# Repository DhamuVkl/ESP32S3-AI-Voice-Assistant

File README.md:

# Design your own AI voice assistant 

*A fully custom, open-source AI voice assistant powered by ESP32-S3 and Xiaozhi AI framework*

</div>

---

## 📋 Overview

This project is a complete DIY AI voice assistant built around the ESP32-S3 microcontroller. It combines custom PCB design, advanced audio processing, and cloud-based AI to create a device that rivals commercial smart speakers in functionality while remaining fully open-source and customizable.

Unlike simple voice-controlled devices, this assistant leverages the **Xiaozhi AI framework** to provide natural language understanding through large language models (LLMs) like Qwen, DeepSeek, and GPT. The system uses a hybrid architecture: lightweight tasks run locally on the ESP32-S3, while computationally intensive AI processing happens on cloud servers.

### Key Highlights

- ✨ **Natural Conversation**: Powered by modern LLMs for intelligent, context-aware responses
- 🎙️ **Dual-Microphone Array**: Advanced audio capture with beamforming and echo cancellation
- 🔋 **Battery Powered**: Complete power management with USB-C charging and portable operation
- 💡 **WS2812B LED Ring**: Visual feedback with customizable animations
- 🏠 **Smart Home Ready**: Integration with Home Assistant and other platforms
- 🔧 **Fully Customizable**: Open hardware and software for endless possibilities
- 📱 **Web-Based Control**: Easy configuration through Xiaozhi console
- 🌐 **Multi-Language**: Support for multiple languages depending on AI model

---

## 🎯 Features

### Hardware Features
- **ESP32-S3-WROOM-1-N16R8** (Dual-core, 16MB Flash, 8MB PSRAM)
- **Dual ICS-43434 MEMS Microphones** for superior audio capture
- **MAX98357A I²S Amplifier** driving 3W speaker
- **BQ24250 Li-Ion Charger** with USB-C power delivery
- **MAX20402 Buck-Boost Regulator** for stable 3.3V output
- **WS2812B RGB LED Ring** for visual status indication
- **Optional OLED Display** header for screen integration
- **Compact PCB Design** (2-layer, professionally fabricated)
- **Custom 3D-Printed Enclosure** optimized for acoustics

### Software Features
- **Wake Word Detection** using Espressif's WakeNet
- **Audio Front-End (AFE)** with noise reduction and echo cancellation
- **WebSocket Communication** for low-latency server connection
- **Multiple AI Models** (Qwen, DeepSeek, GPT-4, and more)
- **Conversation History** and context awareness
- **Voice Profile Support** for personalized responses
- **Smart Home Integration** via Xiaozhi skill marketplace
- **OTA Updates** for firmware upgrades
- **Battery Monitoring** with low-battery alerts

---

## 🛠️ Hardware

### Bill of Materials (BOM)

| Component | Part Number | Quantity | Notes |
|-----------|------------|----------|-------|
| Microcontroller | ESP32-S3-WROOM-1-N16R8 | 1 | Main processor |
| Microphones | TDK InvenSense ICS-43434 | 2 | Digital MEMS |
| Audio Amplifier | MAX98357AETE+ | 1 | Class-D I²S |
| Battery Charger | BQ24250RGER | 1 | Li-Ion charging IC |
| DC-DC Converter | MAX20402ATGA/+ | 1 | Buck-boost regulator |
| RGB LEDs | WS2812B-5050 | 8-12 | Addressable LEDs |
| USB-C Connector | USB4105-GF-A | 1 | Power & programming |
| Speaker | 3W 4Ω Cavity Speaker | 1 | Audio output |
| Battery | Li-Ion/LiPo 3.7V | 1 | 2000-3000mAh recommended |
| Capacitors | Various (0603/0805) | ~25 | See full BOM |
| Resistors | Various (0603) | ~15 | See full BOM |
| Switches | 6x6mm Tactile | 2 | Reset & Boot |
| TVS Diode | USBLC6-2SC6 | 1 | USB ESD protection |

**📥 Full BOM with part numbers**: [Download BOM.csv](Hardware/PCB/BOM/ESP-AI-Assistant-BOM.xlsx)

### PCB Design

The custom PCB is a 2-layer design measuring approximately 80x60mm with careful attention to:
- Signal integrity for I²S audio
- Power distribution with minimal noise
- Thermal management for power ICs
- Acoustic isolation between microphones and speaker

### 3D Enclosure

The enclosure is designed for FDM 3D printing with features for:
- Acoustic optimization (speaker grille, microphone ports)
- LED light diffusion ring
- USB-C and button access
- Battery compartment
- Ventilation slots

## 🚀 Getting Started

### Prerequisites

**Hardware Tools**:
- Soldering iron and supplies
- Multimeter for testing
- USB-C cable (data capable)
- 3D printer (optional, for enclosure)

**Software Requirements**:
- [Visual Studio Code](https://code.visualstudio.com/)
- [ESP-IDF Extension for VS Code](https://marketplace.visualstudio.com/items?itemName=espressif.esp-idf-extension)
- ESP-IDF v5.4 or newer
- Git

### Step 1: Hardware Assembly

1. **Order PCB**: Upload `hardware/gerbers/gerbers.zip` to JLCPCB, PCBWay, or ALLPCB
2. **Source Components**: Use the BOM to order parts from DigiKey, Mouser, or LCSC
3. **Assemble PCB**: Follow the assembly guide for soldering instructions
4. **3D Print Enclosure**: Print the STL files and assemble

### Step 2: WiFi Configuration

On first boot, the device creates a WiFi access point:

1. Connect to WiFi network: `Xioazhi`
2. Navigate to `http://192.168.4.1`
3. Enter your WiFi credentials
4. Device will restart and connect to your network

**Alternative**: Configure WiFi via `idf.py menuconfig` before flashing

### Step 3: Xiaozhi Cloud Setup

1. Create account at [xiaozhi.me](https://xiaozhi.me)
2. Navigate to [Console → Agents](https://xiaozhi.me/console/agents)
3. Click "Add Device" to generate Device ID and Pairing Code
4. Device will auto-pair on first cloud connection
5. Customize AI personality, voice, and skills through console

### Step 4: Test Your Assistant

1. Say the wake word: **"Hey Wanda"**
2. Wait for LED confirmation (blue pulse)
3. Speak your question or command
4. Assistant responds through speaker
5. LED returns to idle state

---

## 🤝 Contributing

Contributions are welcome! Here's how you can help:

### Reporting Bugs
- Use GitHub Issues with detailed reproduction steps
- Include serial monitor logs
- Specify hardware revision and firmware version

### Feature Requests
- Open a GitHub Issue with [Feature Request] tag
- Describe use case and benefits
- Discuss implementation approach

**Contribution Guidelines**: [CONTRIBUTING.md](CONTRIBUTING.md)

---

## 📊 Project Status

- [x] PCB Design and fabrication
- [x] Firmware core functionality
- [x] Xiaozhi cloud integration
- [x] Basic voice interaction
- [x] 3D enclosure design
- [ ] Multi-device mesh networking
- [ ] Offline mode with local LLM
- [ ] Custom wake word training tools
- [ ] Mobile app for configuration
- [ ] Additional language packs

---

## 🔗 Related Projects

- [Xiaozhi ESP32](https://github.com/78/xiaozhi-esp32) - Official Xiaozhi firmware
- [ESP-IDF](https://github.com/espressif/esp-idf) - Espressif IoT Development Framework
- [WakeNet](https://github.com/espressif/esp-sr) - Espressif speech recognition
- [Home Assistant](https://www.home-assistant.io/) - Smart home integration

---

## 📄 License

This project is licensed under the MIT License - see [LICENSE](LICENSE) for details.

### Third-Party Licenses
- ESP-IDF: Apache 2.0
- Xiaozhi Framework: MIT
- Component datasheets: Respective manufacturers

---

## 🙏 Acknowledgments

- **Espressif Systems** for the amazing ESP32-S3 platform and development tools
- **Xiaozhi Team** for creating and maintaining the AI framework
- **Open-source community** for countless libraries and examples
- **PCB manufacturers** (JLCPCB, PCBWay) for affordable prototyping
- **Everyone** who contributed feedback, testing, and improvements

---

**Xiaozhi Community**:
- Forum: [xiaozhi.me/community](https://xiaozhi.me/community)
- Documentation: [docs.xiaozhi.me](https://docs.xiaozhi.me)

<div align="center">

**Built with ❤️ by makers, for makers**

[Documentation](docs/) • [Hardware Files](hardware/) • [Firmware](firmware/) • [Community](https://github.com/yourusername/esp32s3-voice-assistant/discussions)

</div>

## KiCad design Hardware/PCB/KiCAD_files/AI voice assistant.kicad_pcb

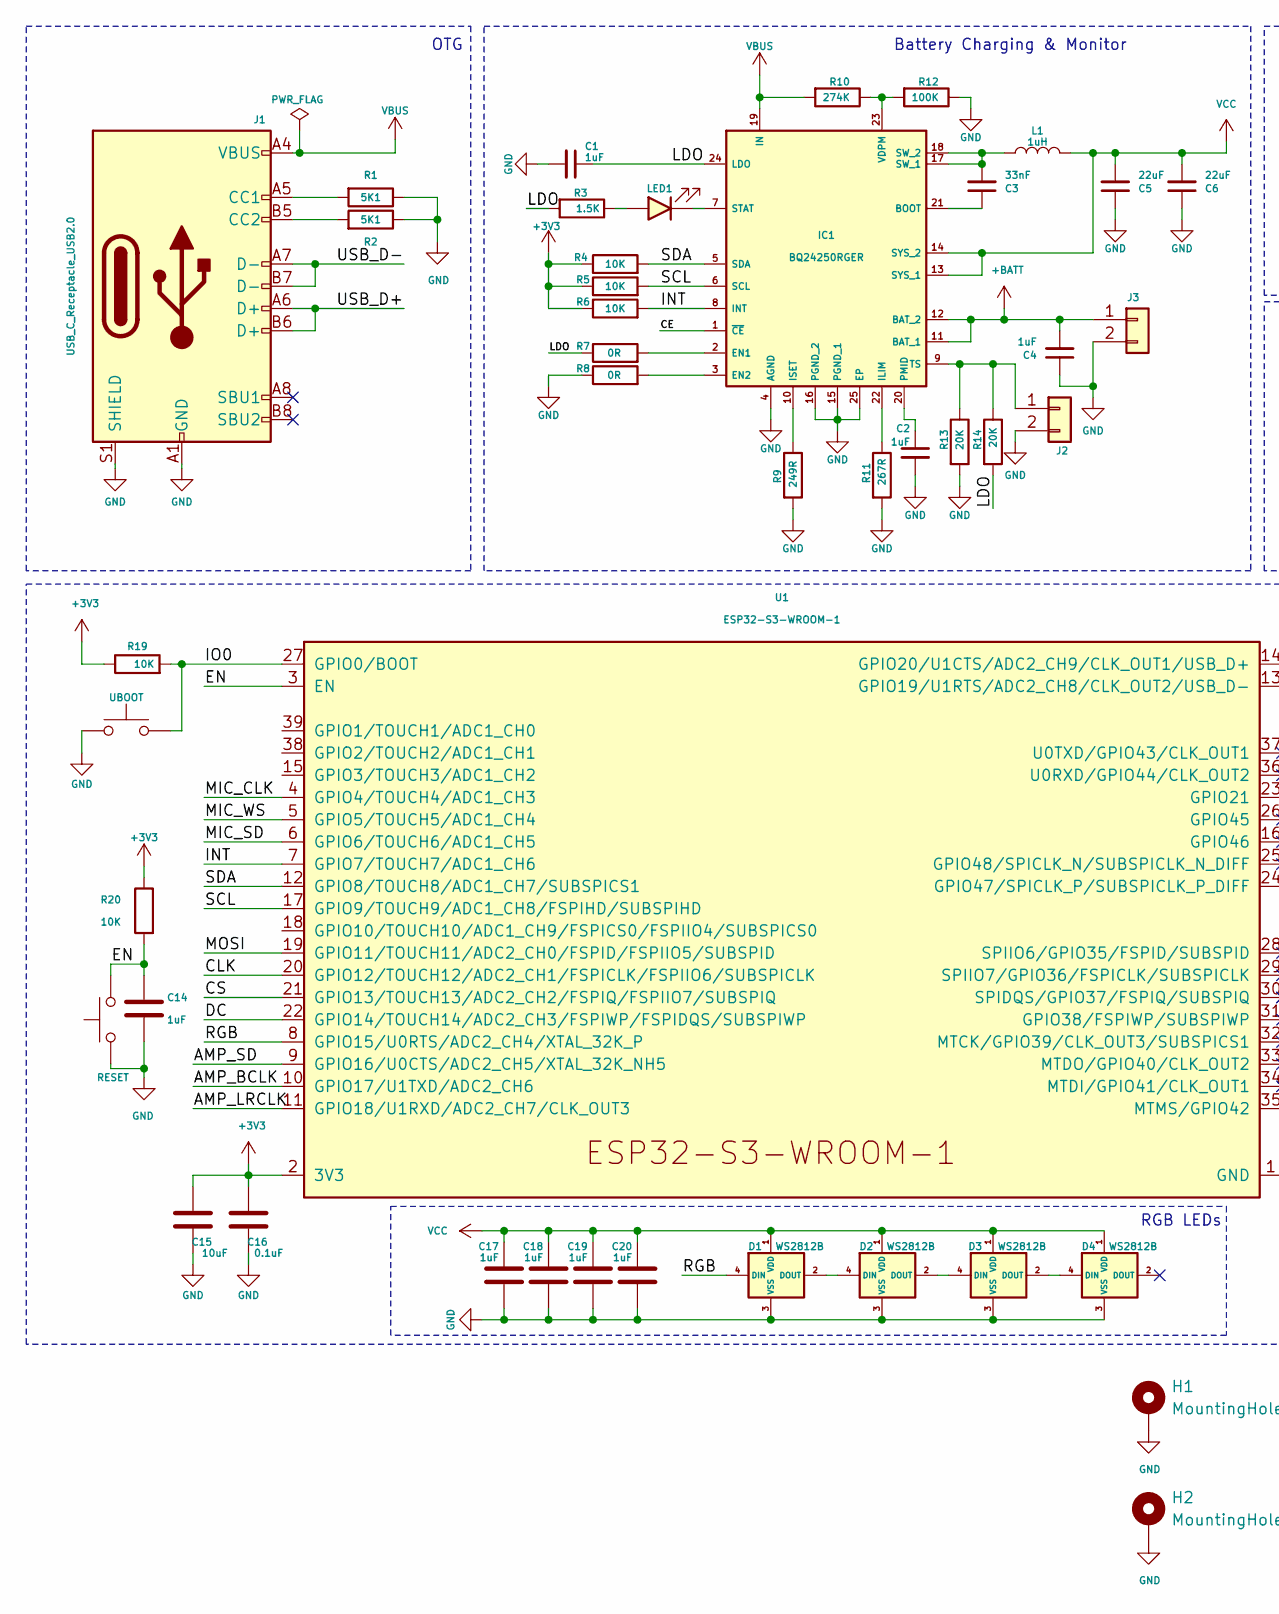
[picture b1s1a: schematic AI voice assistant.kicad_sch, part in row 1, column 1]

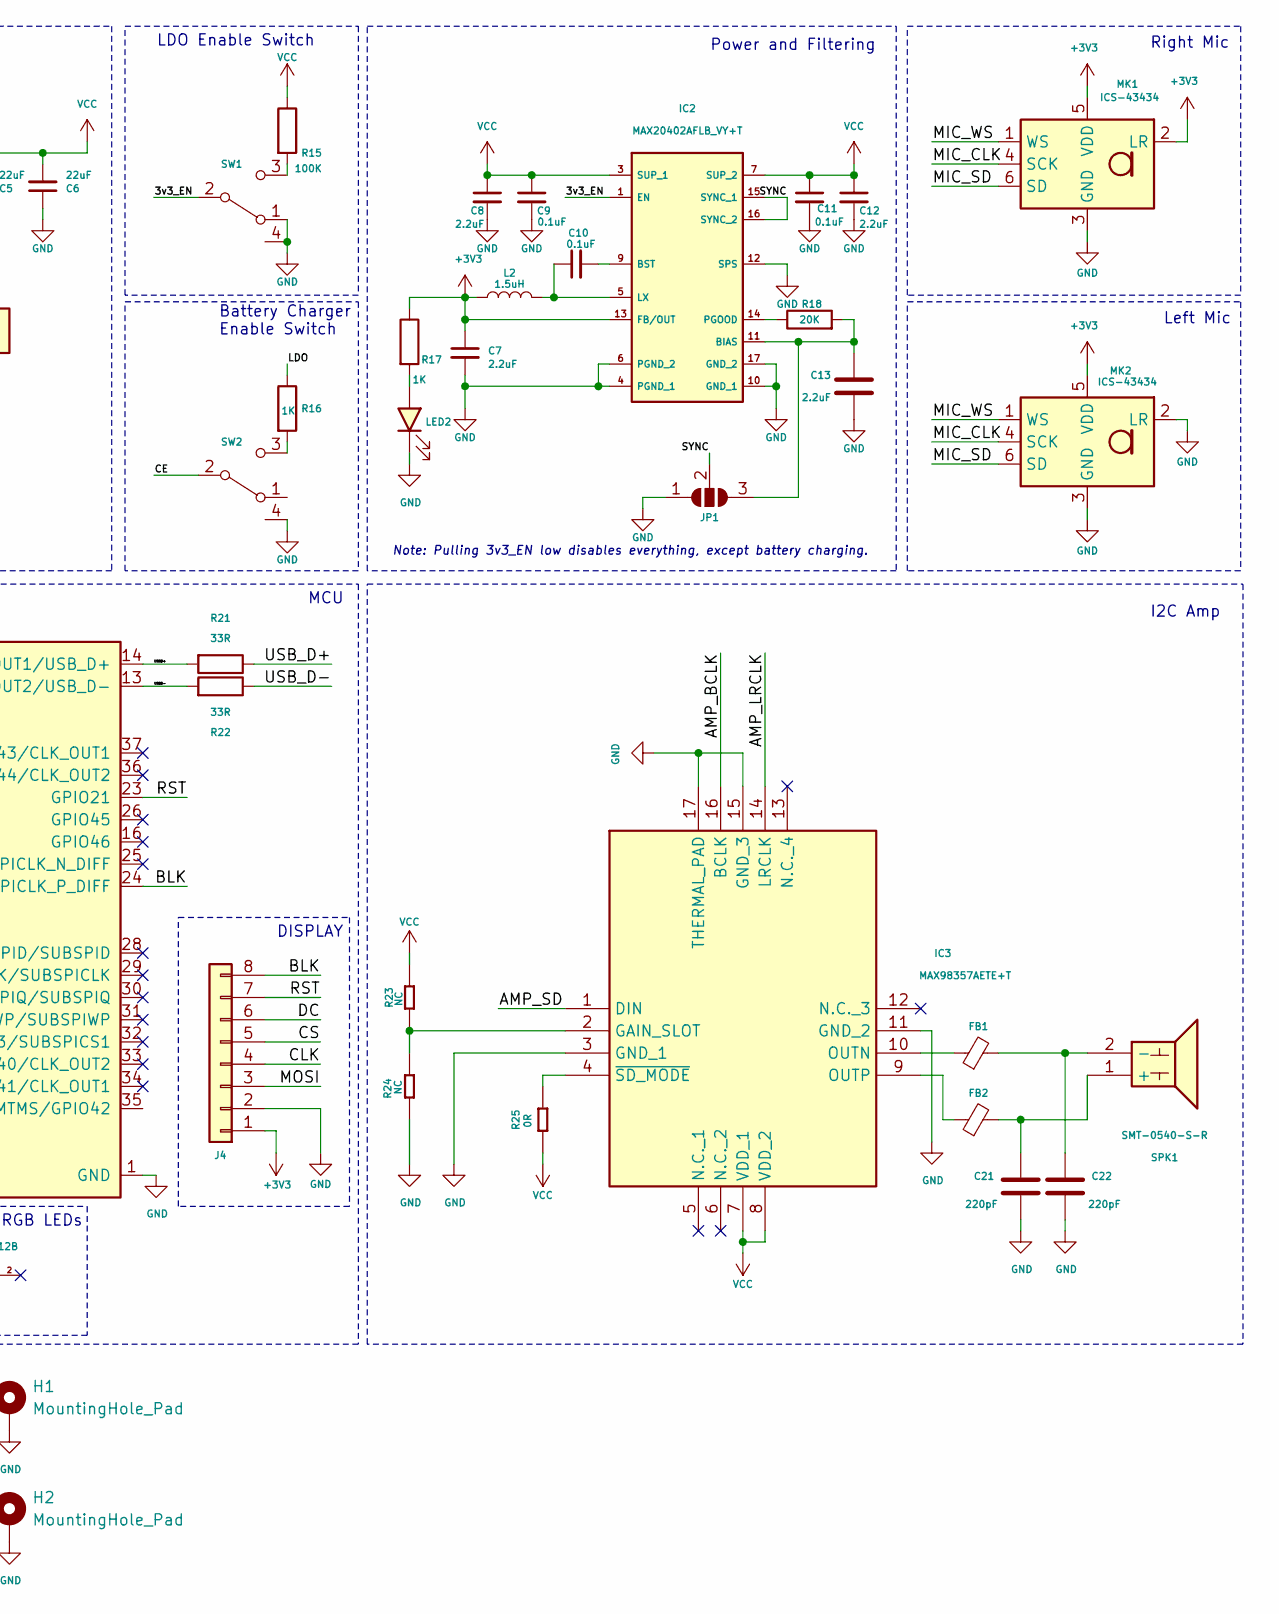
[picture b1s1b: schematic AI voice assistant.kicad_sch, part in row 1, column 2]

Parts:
BOOT1: RESET; Tactile 3x4x2mm TS-A010; DigiKey Part Number 2449-CS1213AGF160CT-ND
BOOT2: UBOOT; Tactile 3x4x2mm TS-A010; DigiKey Part Number 2449-CS1213AGF160CT-ND
C1, C2, C4: 1uF; C_0603_1608Metric
C3: 33nF; C_0603_1608Metric
C5, C6: 22uF; C_0805_2012Metric
C7, C8, C12: 2.2uF; C_0603_1608Metric
C9, C10, C11: 0.1uF; C_0603_1608Metric
C13: 2.2uF; C_0603_1608Metric; DigiKey Part Number 490-6328-1-ND
C14, C17, C18, C19, C20: 1uF; C_0603_1608Metric; DigiKey Part Number 490-6328-1-ND
C15: 10uF; C_0603_1608Metric; DigiKey Part Number 490-6328-1-ND
C16: 0.1uF; C_0603_1608Metric; DigiKey Part Number 490-6328-1-ND
C21, C22: 220pF; C_0603_1608Metric; DigiKey Part Number 490-10018-1-ND
D1, D2, D3, D4: WS2812B; LED_WS2812B_PLCC4_5.0x5.0mm_P3.2mm
FB1, FB2: FerriteBead_Small; L_0805_2012Metric
H1, H2: MountingHole_Pad; MountingHole_2.7mm_M2.5_DIN965_Pad
IC1: BQ24250RGER; QFN50P400X400X100-25N-D; Mouser Part Number 595-BQ24250RGER
IC2: MAX20402AFLB_VY+T; MAX20402AFLBVYT; Mouser Part Number 700-MAX20402AFLBVY+T
IC3: MAX98357AETE+T; QFN50P300X300X80-17N; Mouser Part Number 700-MAX98357AETE+T
J1: USB_C_Receptacle_USB2.0; USB_C_Receptacle_XKB_U262-16XN-4BVC11; DigiKey Part Number 2073-USB4105-GF-ACT-ND
J2, J3: B2B-PH-SM4-TB(LF)(SN); JST_PH_B2B-PH-K_1x02_P2.00mm_Vertical; DigiKey Part Number 455-1704-ND
J4: Conn_01x08; JST_PH_B8B-PH-K_1x08_P2.00mm_Vertical
JP1: SolderJumper_3_Open; SolderJumper-3_P2.0mm_Open_TrianglePad1.0x1.5mm
L1: 1uH; L_Cenker_CKCS6045
L2: 1.5uH; L_Cenker_CKCS5020
LED1, LED2: LED Red; LED_0603_1608Metric; DigiKey Part Number 3147-B1911USD-20D000114U1930CT-ND
MK1, MK2: ICS-43434; InvenSense_ICS-43434-6_3.5x2.65mm
R1, R2: 5K1; R_0603_1608Metric; DigiKey Part Number P5.10KHCT-ND
R3: 1.5K; R_0603_1608Metric; DigiKey Part Number P1.00KHCT-ND
R4, R5, R6: 10K; R_0603_1608Metric; DigiKey Part Number P1.00KHCT-ND
R7, R8: 0R; R_0603_1608Metric; DigiKey Part Number P1.00KHCT-ND
R9: 249R; R_0603_1608Metric; DigiKey Part Number P1.00KHCT-ND
R10: 274K; R_0603_1608Metric; DigiKey Part Number P1.00KHCT-ND
R11: 267R; R_0603_1608Metric; DigiKey Part Number P1.00KHCT-ND
R12: 100K; R_0603_1608Metric; DigiKey Part Number P1.00KHCT-ND
R13, R14, R18: 20K; R_0603_1608Metric; DigiKey Part Number P1.00KHCT-ND
R15: 100K; R_0603_1608Metric; DigiKey Part Number P100KHCT-ND
R16: 1K; R_0603_1608Metric; DigiKey Part Number P100KHCT-ND
R17: 1K; R_0603_1608Metric; DigiKey Part Number P1.00KHCT-ND
R19, R20: 10K; R_0603_1608Metric; DigiKey Part Number P10.0KHCT-ND
R21, R22: 33R; R_0603_1608Metric; DigiKey Part Number P17467CT-ND
R23, R24: NC; R_0603_1608Metric
R25: 0R; R_0603_1608Metric
SPK1: SMT-0540-S-R; JST_PH_B2B-PH-K_1x02_P2.00mm_Vertical; Manufacturer_Part_Number SMT-0540-S-R; DigiKey Part Number 668-1060-1-ND
SW1, SW2: SLW-66527511-SMT-TR; slide switch spdt; DigiKey Part Number 2223-SLW-66527511-SMT-TRCT-ND
U1: ESP32-S3-WROOM-1; DigiKey Part Number 1965-ESP32-S3-WROOM-1-N16R8CT-ND

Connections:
+3V3: C7.1, C15.1, C16.1, IC2.13 (FB/OUT), J4.1, L2.1, MK1.2 (LR), MK1.5 (VDD), MK2.5 (VDD), R4.1, R5.1, R6.1, R17.1, R19.1, R20.1, U1.2 (3V3)
+BATT: C4.2, IC1.11 (BAT_1), IC1.12 (BAT_2), J3.1
/3v3_EN: IC2.1 (EN), SW1.2 (B)
/AMP_BCLK: IC3.16 (BCLK), U1.10 (GPIO17/U1TXD/ADC2_CH6)
/AMP_LRCLK: IC3.14 (LRCLK), U1.11 (GPIO18/U1RXD/ADC2_CH7/CLK_OUT3)
/AMP_SD: IC3.1 (DIN), U1.9 (GPIO16/U0CTS/ADC2_CH5/XTAL_32K_NH5)
/BLK: J4.8, U1.24 (GPIO47/SPICLK_P/SUBSPICLK_P_DIFF)
/CE: IC1.1 (~CE), SW2.2 (B)
/CLK: J4.4, U1.20 (GPIO12/TOUCH12/ADC2_CH1/FSPICLK/FSPIIO6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)
/CS: J4.5, U1.21 (GPIO13/TOUCH13/ADC2_CH2/FSPIQ/FSPIIO7/S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)
/DC: J4.6, U1.22 (GPIO14/TOUCH14/ADC2_CH3/FSPIWP/FSPIDQS/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)
/EN: BOOT1.1, C14.1, R20.2, U1.3 (EN)
/INT: IC1.8 (INT), R6.2, U1.7 (GPIO7/TOUCH7/ADC1_CH6)
/IO0: BOOT2.1, R19.2, U1.27 (GPIO0/BOOT)
/LDO: C1.1, IC1.24 (LDO), R3.2, R7.1, R14.2, R16.1
/MIC_CLK: MK1.4 (SCK), MK2.4 (SCK), U1.4 (GPIO4/TOUCH4/ADC1_CH3)
/MIC_SD: MK1.6 (SD), MK2.6 (SD), U1.6 (GPIO6/TOUCH6/ADC1_CH5)
/MIC_WS: MK1.1 (WS), MK2.1 (WS), U1.5 (GPIO5/TOUCH5/ADC1_CH4)
/MOSI: J4.3, U1.19 (GPIO11/TOUCH11/ADC2_CH0/FSPID/FSPIIO5/S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)
/RGB: D1.4 (DIN), U1.8 (GPIO15/U0RTS/ADC2_CH4/XTAL_32K_P)
/RST: J4.7, U1.23 (GPIO21)
/SCL: IC1.6 (SCL), R5.2, U1.17 (GPIO9/TOUCH9/ADC1_CH8/FSPIHD/SUBSPIHD)
/SDA: IC1.5 (SDA), R4.2, U1.12 (GPIO8/TOUCH8/ADC1_CH7/SUBSPICS1)
/SYNC: IC2.15 (SYNC_1), IC2.16 (SYNC_2), JP1.2 (C)
/USBD+: R21.2, U1.14 (GPIO20/U1CTS/ADC2_CH9/CLK_OUT1/USB_D+)
/USBD-: R22.2, U1.13 (GPIO19/U1RTS/ADC2_CH8/CLK_OUT2/USB_D-)
/USB_D+: J1.A6 (D+), J1.B6 (D+), R21.1
/USB_D-: J1.A7 (D-), J1.B7 (D-), R22.1
GND: BOOT1.2, BOOT2.2, C1.2, C2.2, C4.1, C5.1, C6.1, C7.2, C8.2, C9.2, C11.2, C12.2, C13.2, C14.2, C15.2, C16.2, C17.2, C18.2, C19.2, C20.2, C21.2, C22.2, D1.3 (VSS), D2.3 (VSS), D3.3 (VSS), D4.3 (VSS), H1.1, H2.1, IC1.4 (AGND), IC1.15 (PGND_1), IC1.16 (PGND_2), IC1.25 (EP), IC2.4 (PGND_1), IC2.6 (PGND_2), IC2.10 (GND_1), IC2.12 (SPS), IC2.17 (GND_2), IC3.3 (GND_1), IC3.11 (GND_2), IC3.15 (GND_3), IC3.17 (THERMAL_PAD), J1.A1 (GND), J1.A12 (GND), J1.B1 (GND), J1.B12 (GND), J1.S1 (SHIELD), J2.2, J3.2, J4.2, JP1.1 (A), LED2.1 (K), MK1.3 (GND), MK2.2 (LR), MK2.3 (GND), R1.1, R2.1, R8.1, R9.2, R11.2, R12.1, R13.2, R24.1, SW1.1 (A), SW1.4, SW2.4, U1.1 (GND), U1.40 (GND), U1.41 (GND)
unnamed: D1.2 (DOUT), D2.4 (DIN)
unnamed: D2.2 (DOUT), D3.4 (DIN)
unnamed: D3.2 (DOUT), D4.4 (DIN)
unnamed: C3.1, IC1.21 (BOOT)
unnamed: IC1.2 (EN1), R7.2
unnamed: IC1.3 (EN2), R8.2
unnamed: IC1.22 (ILIM), R11.1
unnamed: IC1.10 (ISET), R9.1
unnamed: C2.1, IC1.20 (PMID)
unnamed: IC1.7 (STAT), LED1.1 (K)
unnamed: C3.2, IC1.17 (SW_1), IC1.18 (SW_2), L1.1
unnamed: IC1.9 (TS), J2.1, R13.1, R14.1
unnamed: IC1.23 (VDPM), R10.1, R12.2
unnamed: C13.1, IC2.11 (BIAS), JP1.3 (B), R18.2
unnamed: C10.2, IC2.9 (BST)
unnamed: C10.1, IC2.5 (LX), L2.2
unnamed: IC2.2 (NC_1), IC2.8 (NC_2)
unnamed: IC2.14 (PGOOD), R18.1
unnamed: IC3.2 (GAIN_SLOT), R23.2, R24.2
unnamed: FB1.1, IC3.10 (OUTN)
unnamed: FB2.1, IC3.9 (OUTP)
unnamed: IC3.4 (~SD_MODE), R25.1
unnamed: J1.A5 (CC1), R1.2
unnamed: J1.B5 (CC2), R2.2
unnamed: LED1.2 (A), R3.1
unnamed: LED2.2 (A), R17.2
unnamed: C21.1, FB2.2, SPK1.1 (+)
unnamed: C22.1, FB1.2, SPK1.2 (-)
unnamed: R15.2, SW1.3 (C)
unnamed: R16.2, SW2.3 (C)
VBUS: IC1.19 (IN), J1.A4 (VBUS), J1.A9 (VBUS), J1.B4 (VBUS), J1.B9 (VBUS), R10.2
VCC: C5.2, C6.2, C8.1, C9.1, C11.1, C12.1, C17.1, C18.1, C19.1, C20.1, D1.1 (VDD), D2.1 (VDD), D3.1 (VDD), D4.1 (VDD), IC1.13 (SYS_1), IC1.14 (SYS_2), IC2.3 (SUP_1), IC2.7 (SUP_2), IC3.7 (VDD_1), IC3.8 (VDD_2), L1.2, R15.1, R23.1, R25.2

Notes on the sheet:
I2C Amp
LDO Enable Switch
Right Mic
Battery Charger Enable Switch
Left Mic
DISPLAY
Note: Pulling 3v3_EN low disables everything, except battery charging.
Power and Filtering
Battery Charging & Monitor
OTG
RGB LEDs
MCU

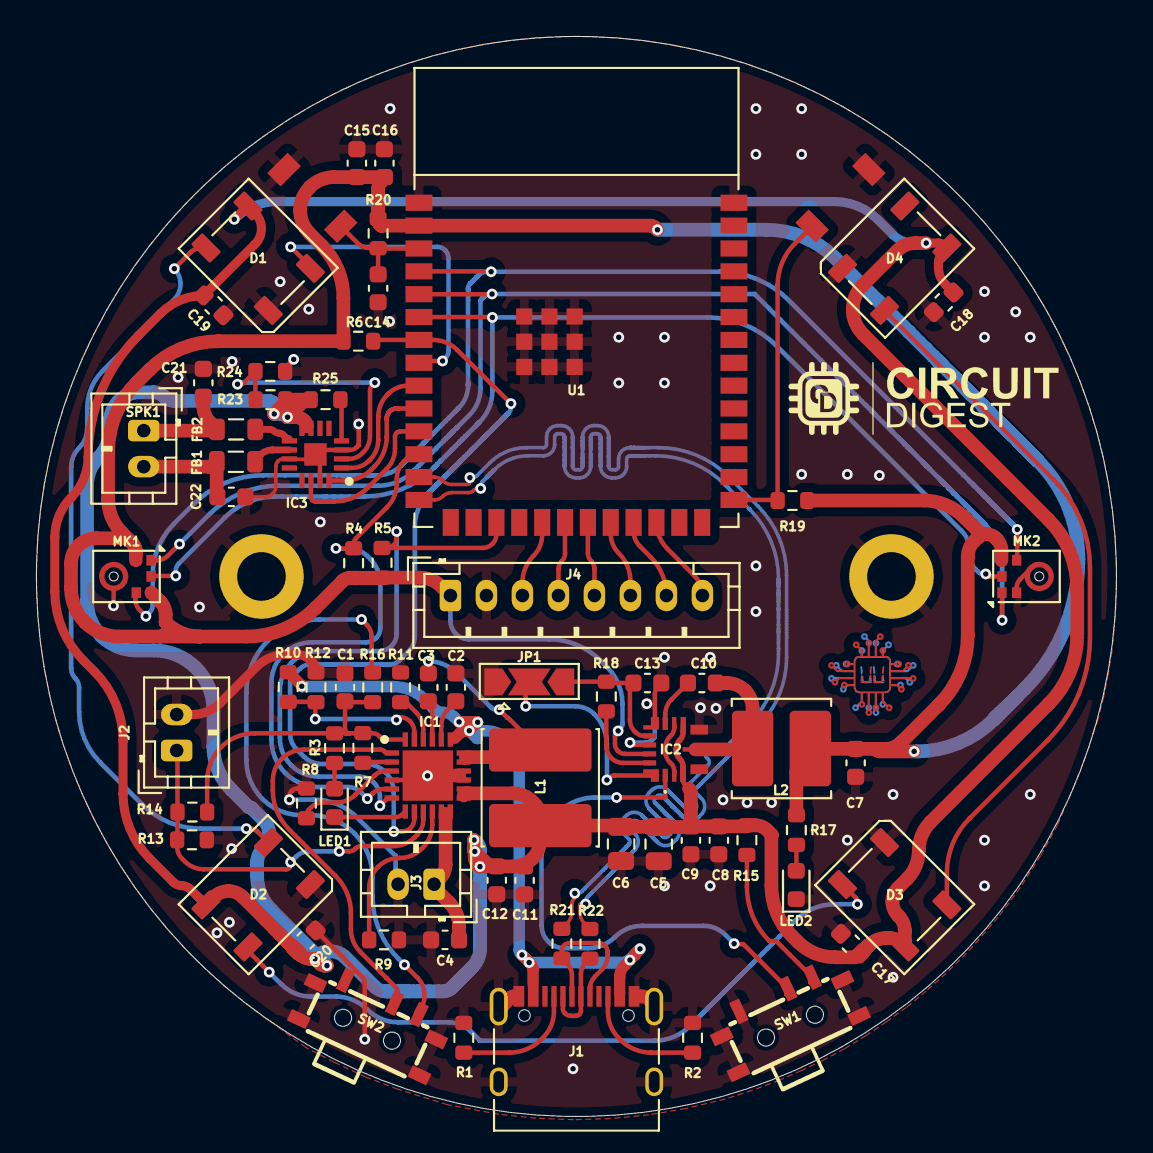
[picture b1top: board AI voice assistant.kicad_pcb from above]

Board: 2 copper layers, 60.0 x 60.0 mm, 75 parts (0 on the bottom side), 61 nets.

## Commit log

2025-10-07 #CSM Hardware Config
2025-11-10 Remove unused dependencies from idf_component.yml
2025-11-10 Refactor LampController constructor for improved readability and correct GPIO initialization
2025-11-10 Add TrafficLightController class for managing traffic light LEDs
2025-11-10 Refactor GPIO pin definitions for clarity and consistency in config.h
2025-11-10 Add TrafficLightController initialization in CompactWifiBoard
2025-11-12 Added CAD models, Schematics and BOM
2025-12-20 feat: Add KiCAD design files
2026-01-31 Refactor code structure for improved readability and maintainability

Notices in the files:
README.md:
License: MIT
